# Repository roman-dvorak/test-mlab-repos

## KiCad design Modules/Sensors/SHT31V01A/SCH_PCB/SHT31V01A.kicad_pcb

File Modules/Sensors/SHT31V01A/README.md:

<!--- PrjInfo ---> <!--- Please remove this line after manually editing --->
<!--- 00a56be08b96043df9e37d6aff7b6990 --->
<!--- Created:20170113-18:25: ---> 
<!--- Author:Mlab: ---> 
<!--- AuthorEmail:mlab@mlab.cz: ---> 
<!--- Tags:imported: ---> 
<!--- Ust:http://www.ust.cz/shop/product_info.php?cPath=22_28&products_id=267: ---> 
<!--- Label --->
<!--- ELabel ---> 
<!--- Name:SHT31V01A: --->
#SHT31V01A 
<!--- LongName --->
Digital sensor relative humidity and temperature
<!--- ELongName ---> 

<!--- Lead --->
SHT31 sensor module which measures relative humidity from 0% to 100% with an accuracy of + / - 2%. Temperature is measured in the range -40 ° C to 125 ° C with a  an accuracy of 0.3 ° C.
<!--- ELead ---> 

<!--- Description --->
<!--- EDescription --->
<!--- Content --->
<!--- EContent --->

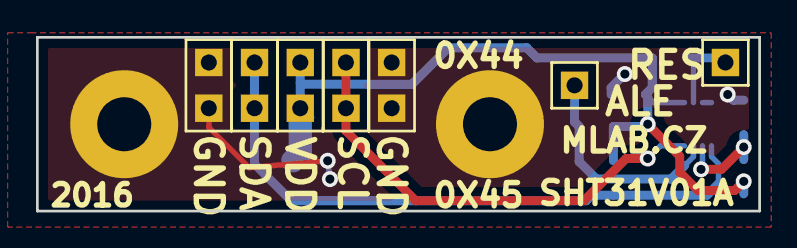
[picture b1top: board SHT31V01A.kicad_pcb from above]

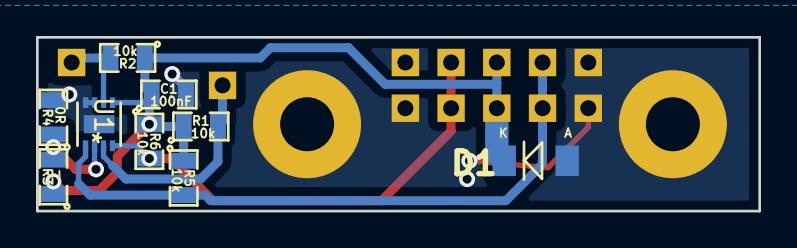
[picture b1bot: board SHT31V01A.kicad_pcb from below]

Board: 2 copper layers, 40.1 x 9.7 mm, 18 parts (9 on the bottom side), 7 nets.

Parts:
C1: 100nF; SMD-0805
D1: BZV55C-5,6V; Diode-MiniMELF_Standard
J1, J2: CONN1_1; Straight_1x01
J9, J10, J11, J12, J13: JUMP_2x1; Straight_1x02
M1, M2: HOLE; MountingHole_3mm
R1, R2, R5, R6: 10k; SMD-0805
R3: -; SMD-0805
R4: 0R; SMD-0805
U1: SHT31; DFN-8-1EP_2.4x2.4mm_Pitch0.5mm

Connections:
+3V3: C1.1, D1.2, J9.1, J9.2, R1.1, R2.1, R3.1, R5.1, R6.1, U1.5
/ALERT: J1.1, R1.2, U1.3
/SCL: J11.1, J11.2, R6.2, U1.4
/SDA: J10.1, J10.2, R5.2, U1.1
/nRESET: J2.1, R2.2, U1.6
GND: C1.2, D1.1, J12.1, J12.2, J13.1, J13.2, M1.1, M2.1, R4.2, U1.7, U1.8, U1.9
unnamed: R3.2, R4.1, U1.2

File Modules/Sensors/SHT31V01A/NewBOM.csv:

1;"D1";"Mlab_D:Diode-MiniMELF_Standard";1;"BZV55C-5,6V"
2;"U1";"Mlab_IO:DFN-8-1EP_2.4x2.4mm_Pitch0.5mm";1;"SHT31"
3;"M1";"Mlab_Mechanical:MountingHole_3mm";2;"HOLE"
4;"J1";"Mlab_Pin_Headers:Straight_1x01";2;"CONN1_1"
5;"J10";"Mlab_Pin_Headers:Straight_1x02";5;"JUMP_2x1"
6;"C1";"Mlab_R:SMD-0805";7;"100nF"

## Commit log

2016-12-30 1st test
2016-12-31 testovaci skript na generovani vyrobnich dat z kicadu
2016-12-31 add grb files
2016-12-31 BOM generator
2016-12-31 add svg scheme
2017-01-01 readme md -> pdf
2017-01-01 working dic
2017-01-01 add preview
2017-01-01 new generator
2017-01-01 Lines wrapping modified.
2017-01-02 git push auto readme
2017-01-02 Lead Img
2017-01-02 add pdf
2017-01-02 auto gen line
2017-02-10 Creates book.json
    Auto commit by GitBook Editor
